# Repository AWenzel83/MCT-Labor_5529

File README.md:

# MCT-Labor_5529
Laboraufbau mit MSP-EXP430f5529-LP

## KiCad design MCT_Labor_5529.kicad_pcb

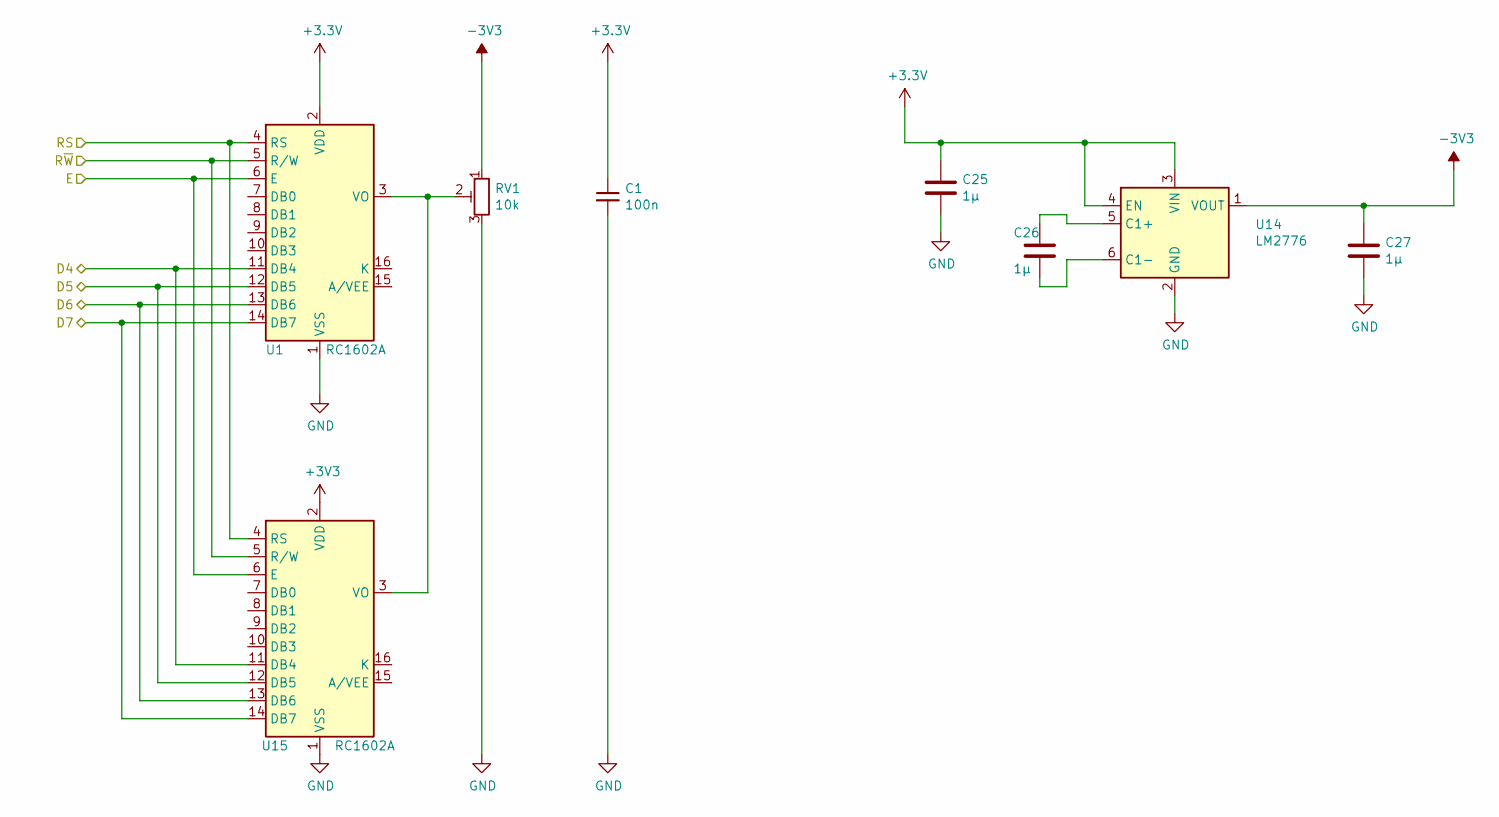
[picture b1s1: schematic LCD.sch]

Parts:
C1: 100n; C_0603_1608Metric_Pad1.05x0.95mm_HandSolder
C25, C26, C27: 1µ; C_0603_1608Metric_Pad1.05x0.95mm_HandSolder
RV1: 10k; Potentiometer_Bourns_3296P_Horizontal
U1: RC1602A; WC1602A
U14: LM2776; SOT-23-6
U15: RC1602A

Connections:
-3V3: C27.1, RV1.1, U14.1 (VOUT)
/LCD/D4: U1.11 (DB4), U15.11 (DB4); also elsewhere on the board
/LCD/D5: U1.12 (DB5), U15.12 (DB5); also elsewhere on the board
/LCD/D6: U1.13 (DB6), U15.13 (DB6); also elsewhere on the board
/LCD/D7: U1.14 (DB7), U15.14 (DB7); also elsewhere on the board
/LCD/E: U1.6 (E), U15.6 (E); also elsewhere on the board
/Launchpad/P6.4: U1.5 (R/W), U15.5 (R/W); also elsewhere on the board
/Launchpad/P6.5: U1.4 (RS), U15.4 (RS); also elsewhere on the board
unnamed: C26.1, U14.5 (C1+)
unnamed: C26.2, U14.6 (C1-)
unnamed: RV1.2, U1.3 (VO), U15.3 (VO)

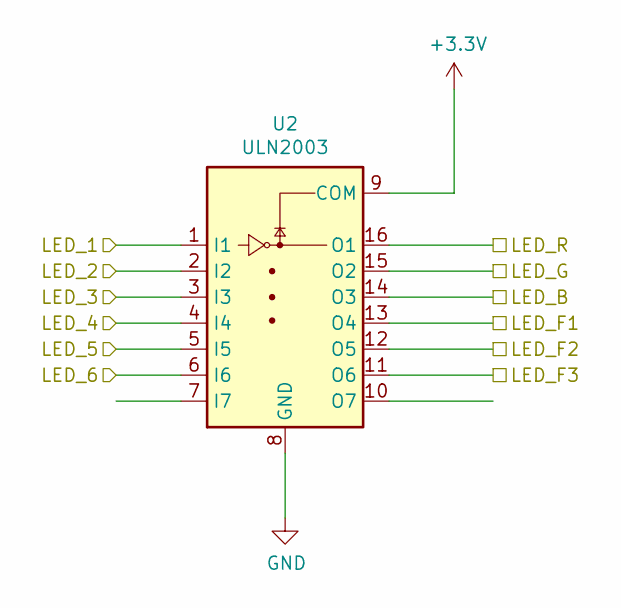
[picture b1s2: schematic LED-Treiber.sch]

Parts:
U2: ULN2003; SOIC-16_3.9x9.9mm_P1.27mm

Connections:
/Button_decoder/LED_F1: U2.13 (O4); also elsewhere on the board
/Button_decoder/LED_F2: U2.12 (O5); also elsewhere on the board
/Button_decoder/LED_F3: U2.11 (O6); also elsewhere on the board
/LED-Treiber/LED_1: U2.1 (I1); also elsewhere on the board
/LED-Treiber/LED_2: U2.2 (I2); also elsewhere on the board
/LED-Treiber/LED_3: U2.3 (I3); also elsewhere on the board
/LED-Treiber/LED_4: U2.4 (I4); also elsewhere on the board
/LED-Treiber/LED_5: U2.5 (I5); also elsewhere on the board
/LED-Treiber/LED_6: U2.6 (I6); also elsewhere on the board
/LED-Treiber/LED_B: U2.14 (O3); also elsewhere on the board
/LED-Treiber/LED_G: U2.15 (O2); also elsewhere on the board
/LED-Treiber/LED_R: U2.16 (O1); also elsewhere on the board

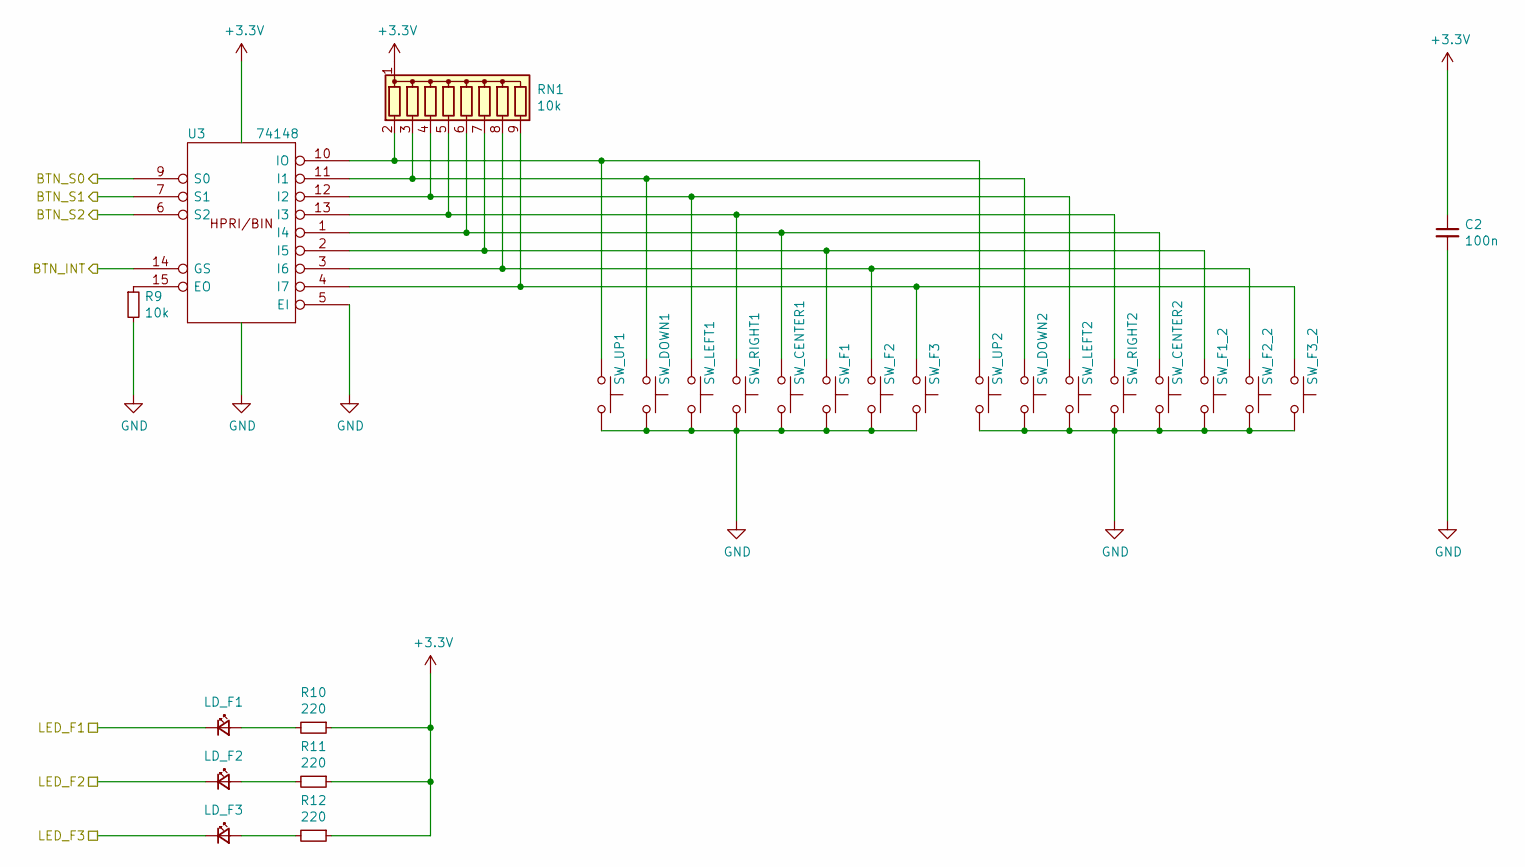
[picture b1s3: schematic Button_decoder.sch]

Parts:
C2: 100n; C_0603_1608Metric_Pad1.05x0.95mm_HandSolder
LD_F1, LD_F2, LD_F3: LED_Small; LED_D3.0mm
R9: 10k; R_0603_1608Metric_Pad1.05x0.95mm_HandSolder
R10, R11, R12: 220; R_0603_1608Metric_Pad1.05x0.95mm_HandSolder
RN1: 10k; R_Array_SIP9
SW_CENTER1: SW_MEC_5G; SW_MEC_5GSH9
SW_CENTER2: SW_MEC_5G; SW_SPST_Omron_B3FS-100xP
SW_DOWN1: SW_MEC_5G; SW_MEC_5GSH9
SW_DOWN2: SW_MEC_5G; SW_SPST_Omron_B3FS-100xP
SW_F1, SW_F2, SW_F3: SW_MEC_5G; SW_MEC_5GSH9
SW_F1_2: SW_MEC_5; SW_SPST_Omron_B3FS-100xP
SW_F2_2, SW_F3_2: SW_MEC_5G; SW_SPST_Omron_B3FS-100xP
SW_LEFT1: SW_MEC_5G; SW_MEC_5GSH9
SW_LEFT2: SW_MEC_5G; SW_SPST_Omron_B3FS-100xP
SW_RIGHT1: SW_MEC_5G; SW_MEC_5GSH9
SW_RIGHT2: SW_MEC_5G; SW_SPST_Omron_B3FS-100xP
SW_UP1: SW_MEC_5G; SW_MEC_5GSH9
SW_UP2: SW_MEC_5G; SW_SPST_Omron_B3FS-100xP
U3: 74148; SOIC-16_3.9x9.9mm_P1.27mm

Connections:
/Button_decoder/BTN_INT: U3.14 (GS); also elsewhere on the board
/Button_decoder/BTN_S0: U3.9 (S0); also elsewhere on the board
/Button_decoder/BTN_S1: U3.7 (S1); also elsewhere on the board
/Button_decoder/BTN_S2: U3.6 (S2); also elsewhere on the board
/Button_decoder/LED_F1: LD_F1.1 (K); also elsewhere on the board
/Button_decoder/LED_F2: LD_F2.1 (K); also elsewhere on the board
/Button_decoder/LED_F3: LD_F3.1 (K); also elsewhere on the board
unnamed: LD_F1.2 (A), R10.2
unnamed: LD_F2.2 (A), R11.2
unnamed: LD_F3.2 (A), R12.2
unnamed: R9.1, U3.15 (EO)
unnamed: RN1.2 (R1), SW_UP1.1 (A), SW_UP1.2 (A), SW_UP2.1 (A), SW_UP2.2 (A), U3.10 (IO)
unnamed: RN1.3 (R2), SW_DOWN1.1 (A), SW_DOWN1.2 (A), SW_DOWN2.1 (A), SW_DOWN2.2 (A), U3.11 (I1)
unnamed: RN1.4 (R3), SW_LEFT1.1 (A), SW_LEFT1.2 (A), SW_LEFT2.1 (A), SW_LEFT2.2 (A), U3.12 (I2)
unnamed: RN1.5 (R4), SW_RIGHT1.1 (A), SW_RIGHT1.2 (A), SW_RIGHT2.1 (A), SW_RIGHT2.2 (A), U3.13 (I3)
unnamed: RN1.6 (R5), SW_CENTER1.1 (A), SW_CENTER1.2 (A), SW_CENTER2.1 (A), SW_CENTER2.2 (A), U3.1 (I4)
unnamed: RN1.7 (R6), SW_F1.1 (A), SW_F1.2 (A), SW_F1_2.1 (A), SW_F1_2.2 (A), U3.2 (I5)
unnamed: RN1.8 (R7), SW_F2.1 (A), SW_F2.2 (A), SW_F2_2.1 (A), SW_F2_2.2 (A), U3.3 (I6)
unnamed: RN1.9 (R8), SW_F3.1 (A), SW_F3.2 (A), SW_F3_2.1 (A), SW_F3_2.2 (A), U3.4 (I7)

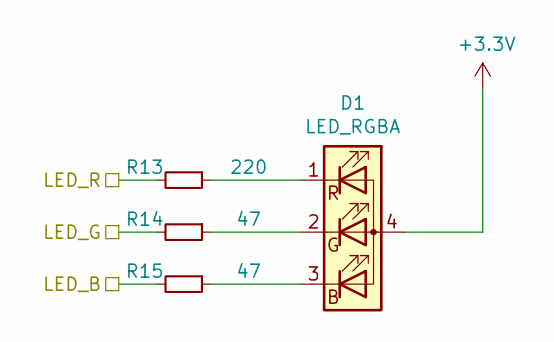
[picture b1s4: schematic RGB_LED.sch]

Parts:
D1: LED_RGBA; LED_Cree-PLCC4_3.2x2.8mm_CCW
R13: 220; R_0603_1608Metric_Pad1.05x0.95mm_HandSolder
R14, R15: 47; R_0603_1608Metric_Pad1.05x0.95mm_HandSolder

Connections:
/LED-Treiber/LED_B: R15.2; also elsewhere on the board
/LED-Treiber/LED_G: R14.2; also elsewhere on the board
/LED-Treiber/LED_R: R13.2; also elsewhere on the board
unnamed: D1.1 (RK), R13.1
unnamed: D1.2 (GK), R14.1
unnamed: D1.3 (BK), R15.1

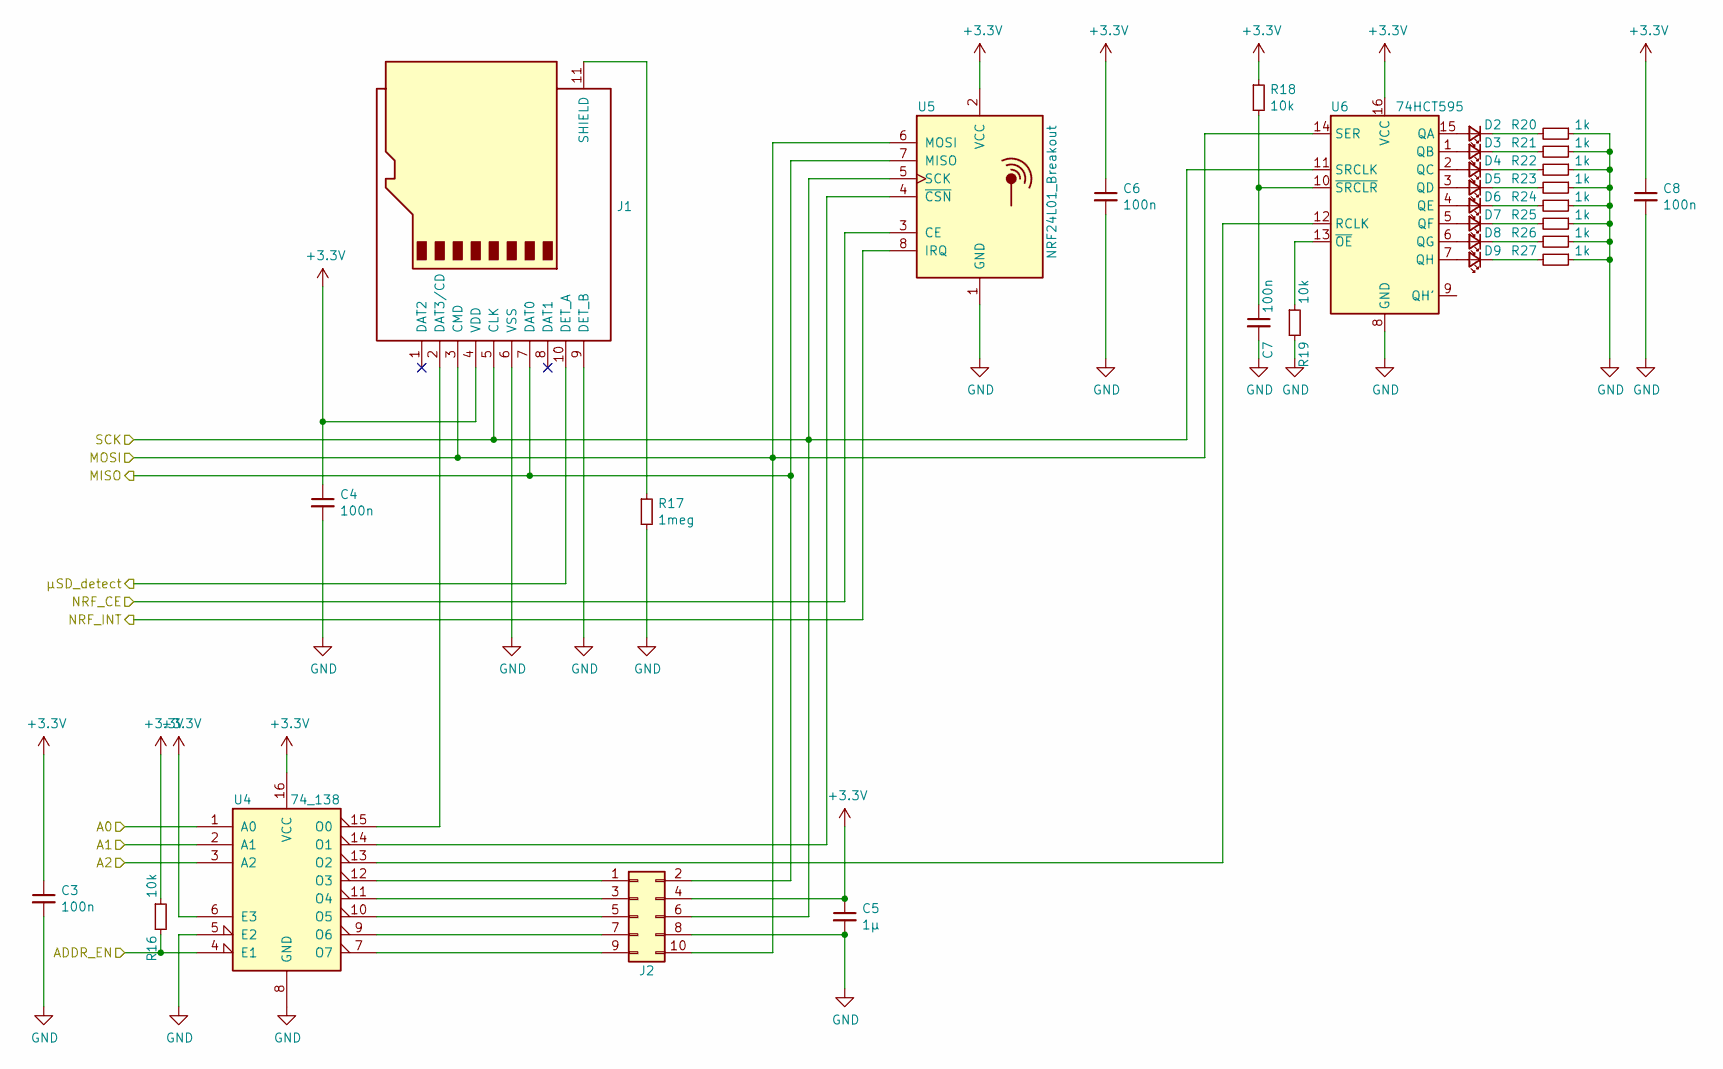
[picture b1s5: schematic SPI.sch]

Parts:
C3, C4, C6, C7, C8: 100n; C_0603_1608Metric_Pad1.05x0.95mm_HandSolder
C5: 1µ; C_0603_1608Metric_Pad1.05x0.95mm_HandSolder
D2, D3, D4, D5, D6, D7, D8, D9: LED_Small; LED_0603_1608Metric_Pad1.05x0.95mm_HandSolder
J1: Micro_SD_Card_Det; microSD_HC_Hirose_DM3D-SF
J2: Conn_02x05_Odd_Even; PinHeader_2x05_P2.54mm_Vertical
R16, R18, R19: 10k; R_0603_1608Metric_Pad1.05x0.95mm_HandSolder
R17: 1meg; R_0603_1608Metric_Pad1.05x0.95mm_HandSolder
R20, R21, R22, R23, R24, R25, R26, R27: 1k; R_0603_1608Metric_Pad1.05x0.95mm_HandSolder
U4: 74_138; SOIC-16_3.9x9.9mm_P1.27mm
U5: NRF24L01_Breakout; nRF24L01_Breakout
U6: 74HCT595; SOIC-16_3.9x9.9mm_P1.27mm

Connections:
/Launchpad/P3.2: J1.5 (CLK), J2.6, U5.5 (SCK), U6.11 (SRCLK); also elsewhere on the board
/Launchpad/P7.4: J1.10 (DET_A); also elsewhere on the board
/SPI/A0: U4.1 (A0); also elsewhere on the board
/SPI/A1: U4.2 (A1); also elsewhere on the board
/SPI/A2: U4.3 (A2); also elsewhere on the board
/SPI/ADDR_EN: R16.2, U4.4 (E1); also elsewhere on the board
/SPI/MISO: J1.7 (DAT0), J2.2, U5.7 (MISO); also elsewhere on the board
/SPI/MOSI: J1.3 (CMD), J2.10, U5.6 (MOSI), U6.14 (SER); also elsewhere on the board
/SPI/NRF_CE: U5.3 (CE); also elsewhere on the board
/SPI/NRF_INT: U5.8 (IRQ); also elsewhere on the board
unnamed: C7.1, R18.2, U6.10 (~SRCLR)
unnamed: D2.1 (K), R20.2
unnamed: D2.2 (A), U6.15 (QA)
unnamed: D3.1 (K), R21.2
unnamed: D3.2 (A), U6.1 (QB)
unnamed: D4.1 (K), R22.2
unnamed: D4.2 (A), U6.2 (QC)
unnamed: D5.1 (K), R23.2
unnamed: D5.2 (A), U6.3 (QD)
unnamed: D6.1 (K), R24.2
unnamed: D6.2 (A), U6.4 (QE)
unnamed: D7.1 (K), R25.2
unnamed: D7.2 (A), U6.5 (QF)
unnamed: D8.1 (K), R26.2
unnamed: D8.2 (A), U6.6 (QG)
unnamed: D9.1 (K), R27.2
unnamed: D9.2 (A), U6.7 (QH)
unnamed: J1.2 (DAT3/CD), U4.15 (O0)
unnamed: J1.11 (SHIELD), R17.1
unnamed: J2.1, U4.12 (O3)
unnamed: J2.3, U4.11 (O4)
unnamed: J2.5, U4.10 (O5)
unnamed: J2.7, U4.9 (O6)
unnamed: J2.9, U4.7 (O7)
unnamed: R19.1, U6.13 (~OE)
unnamed: U4.13 (O2), U6.12 (RCLK)
unnamed: U4.14 (O1), U5.4 (~CSN)

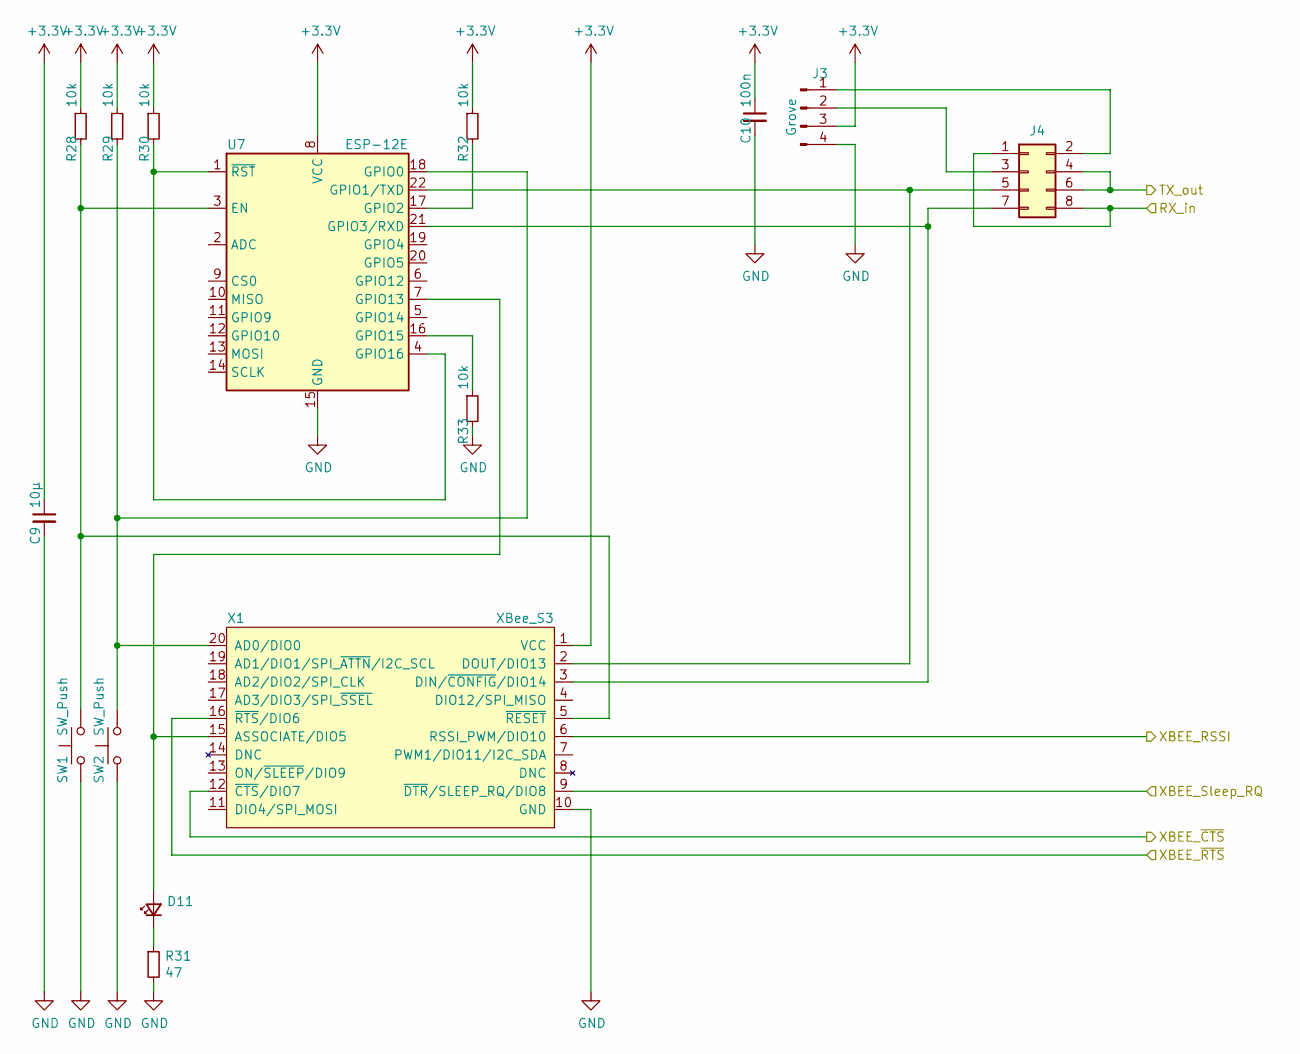
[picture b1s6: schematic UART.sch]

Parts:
C9: 10µ; C_1206_3216Metric_Pad1.42x1.75mm_HandSolder
C10: 100n; C_0603_1608Metric_Pad1.05x0.95mm_HandSolder
D11: LED_Small; LED_0603_1608Metric_Pad1.05x0.95mm_HandSolder
J3: Grove; NS-Tech_Grove_1x04_P2mm_Vertical
J4: Conn_02x04_Odd_Even; PinHeader_2x04_P2.54mm_Vertical
R28, R29, R30, R32, R33: 10k; R_0603_1608Metric_Pad1.05x0.95mm_HandSolder
R31: 47; R_0603_1608Metric_Pad1.05x0.95mm_HandSolder
SW1, SW2: SW_Push; SW_Tactile_SPST_Angled_PTS645Vx39-2LFS
U7: ESP-12E
X1: XBee_S3; XBEE_THT

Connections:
/Launchpad/P1.2_XBEE: X1.9 (~DTR~/SLEEP_RQ/DIO8); also elsewhere on the board
/Launchpad/P1.3_XBEE: X1.12 (~CTS~/DIO7); also elsewhere on the board
/Launchpad/P1.4_XBEE: X1.16 (~RTS~/DIO6); also elsewhere on the board
/Launchpad/P1.5_XBEE: X1.6 (RSSI_PWM/DIO10); also elsewhere on the board
/Launchpad/P3.3: J4.1, J4.8; also elsewhere on the board
/Launchpad/P3.4: J4.4, J4.6; also elsewhere on the board
unnamed: D11.1 (K), R31.1
unnamed: J3.1, J4.2
unnamed: J3.2, J4.3
unnamed: R28.2, SW1.2, U7.3 (EN), X1.5 (~RESET)

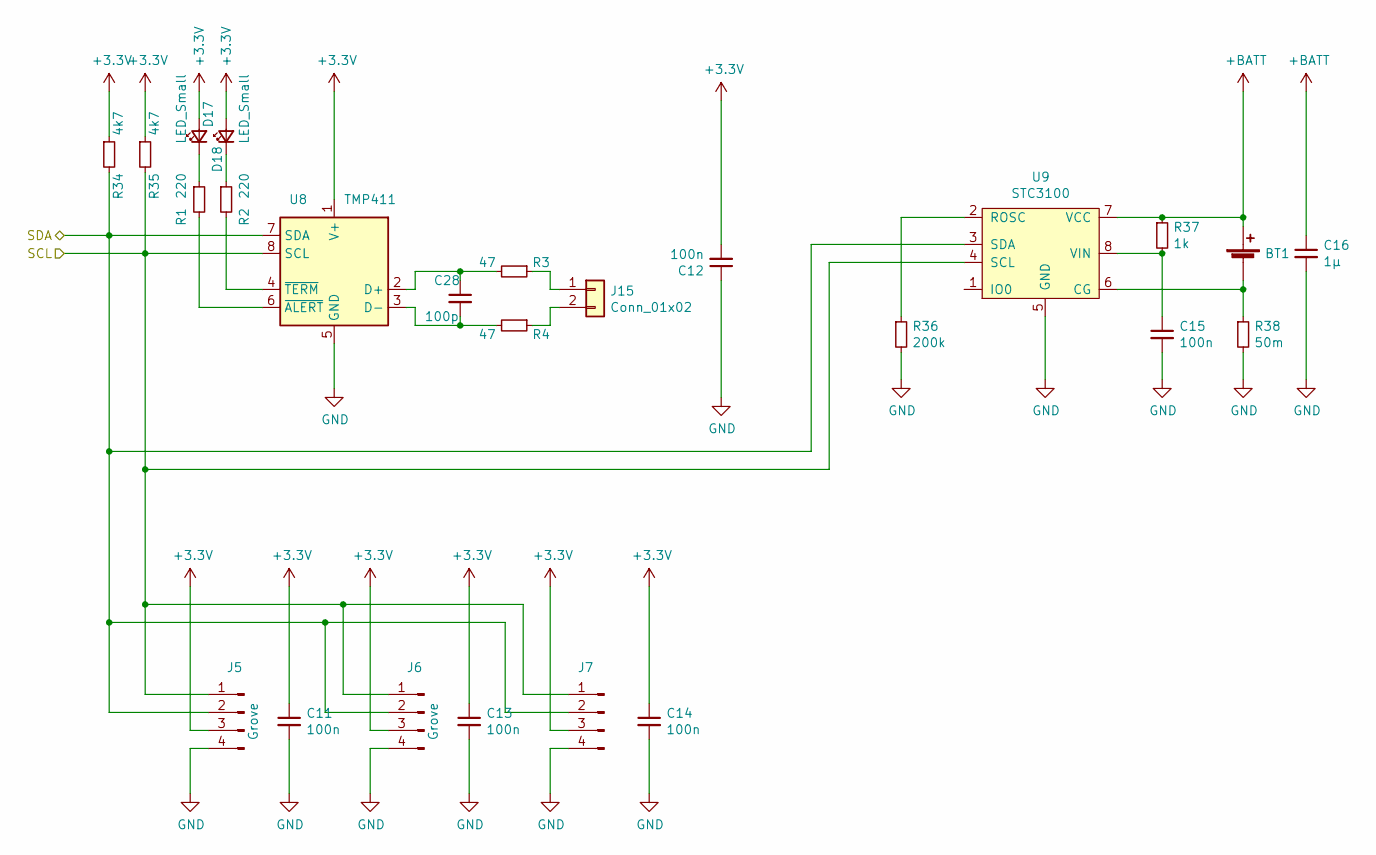
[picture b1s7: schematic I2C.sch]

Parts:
BT1: 18650_Cell; BatteryHolder_Keystone_1042_1x18650
C11, C12, C13, C14, C15: 100n; C_0603_1608Metric_Pad1.05x0.95mm_HandSolder
C16: 1µ; C_0603_1608Metric_Pad1.05x0.95mm_HandSolder
C28: 100p; C_0603_1608Metric_Pad1.05x0.95mm_HandSolder
D17, D18: LED_Small; LED_0603_1608Metric_Pad1.05x0.95mm_HandSolder
J5, J6: Grove; NS-Tech_Grove_1x04_P2mm_Vertical
J7: Conn_01x04_Male; PinHeader_1x04_P2.54mm_Vertical
J15: Conn_01x02; PinHeader_1x02_P2.54mm_Vertical
R1, R2: 220; R_0603_1608Metric_Pad1.05x0.95mm_HandSolder
R3, R4: 47; R_0603_1608Metric_Pad1.05x0.95mm_HandSolder
R34, R35: 4k7; R_0603_1608Metric_Pad1.05x0.95mm_HandSolder
R36: 200k; R_0603_1608Metric_Pad1.05x0.95mm_HandSolder
R37: 1k; R_0603_1608Metric_Pad1.05x0.95mm_HandSolder
R38: 50m; R_1206_3216Metric_Pad1.42x1.75mm_HandSolder
U8: TMP411; SO-8_3.9x4.9mm_P1.27mm
U9: STC3100; MSOP-8_3x3mm_P0.65mm

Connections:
+BATT: BT1.1 (+), C16.1, R37.1, U9.7 (VCC); also elsewhere on the board
/Launchpad/P4.1: J5.2, J6.2, J7.2, R34.2, U8.7 (SDA), U9.3 (SDA); also elsewhere on the board
/Launchpad/P4.2: J5.1, J6.1, J7.1, R35.2, U8.8 (SCL), U9.4 (SCL); also elsewhere on the board
unnamed: BT1.2 (-), R38.1, U9.6 (CG)
unnamed: C15.1, R37.2, U9.8 (VIN)
unnamed: C28.1, R3.2, U8.2 (D+)
unnamed: C28.2, R4.2, U8.3 (D-)
unnamed: D17.1 (K), R1.1
unnamed: D18.1 (K), R2.1
unnamed: J15.1, R3.1
unnamed: J15.2, R4.1
unnamed: R1.2, U8.6 (~ALERT)
unnamed: R2.2, U8.4 (~TERM)
unnamed: R36.1, U9.2 (ROSC)

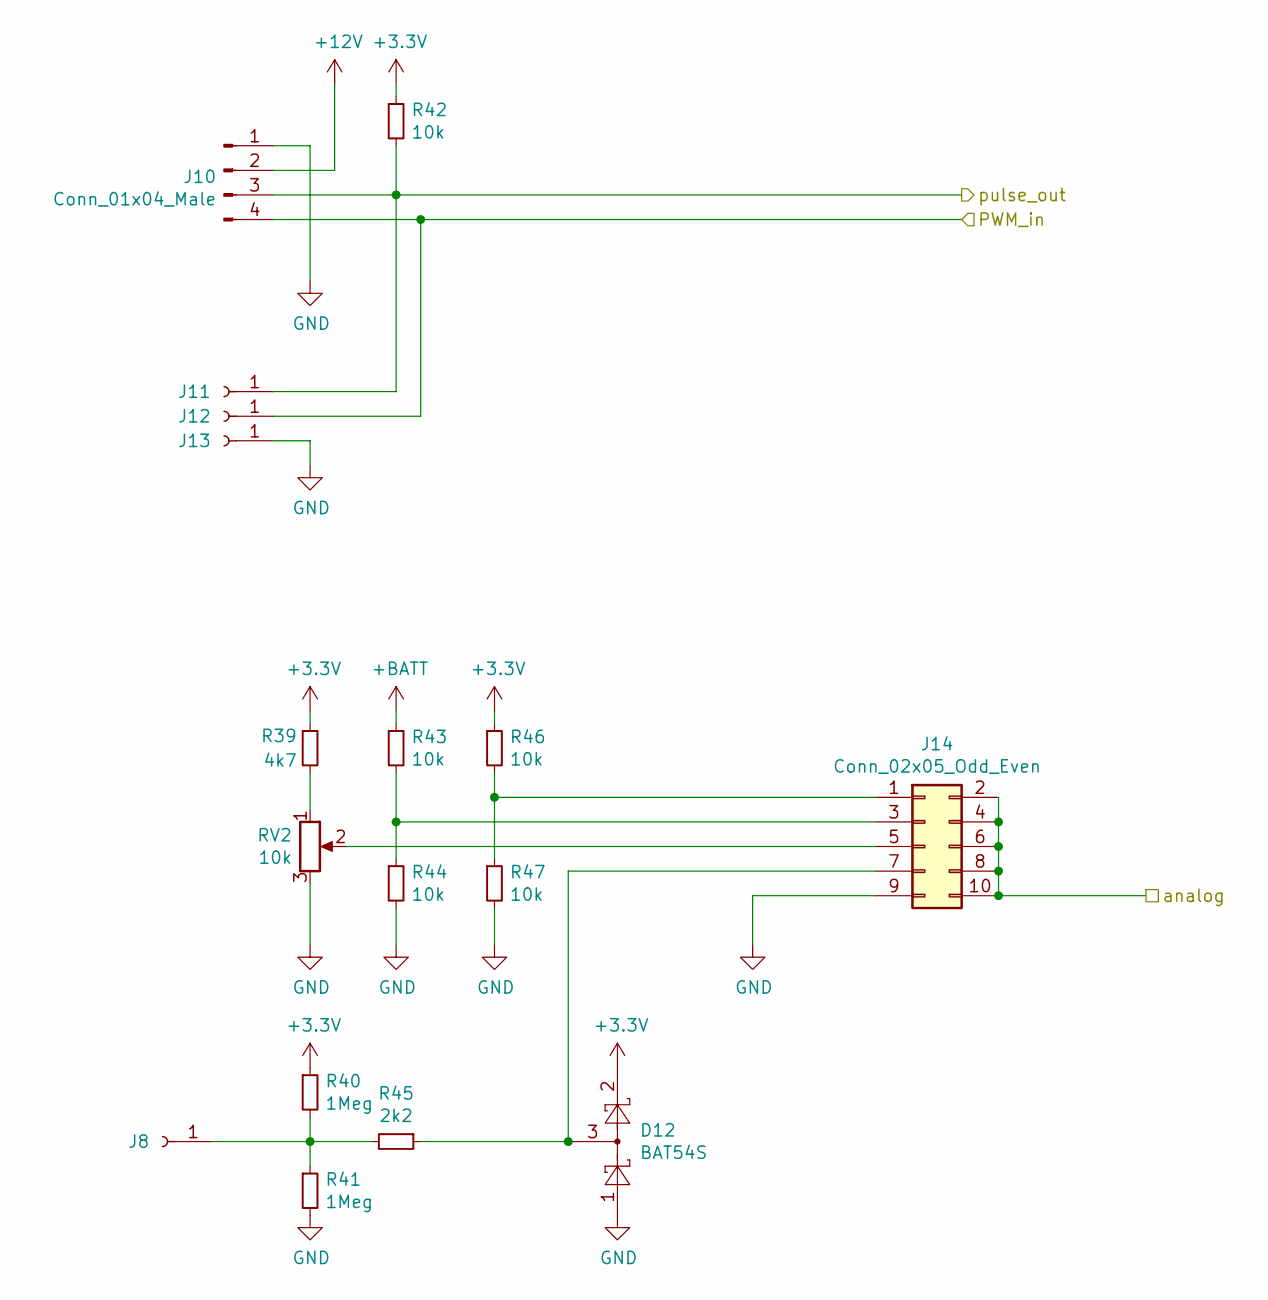
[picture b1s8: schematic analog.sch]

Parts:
D12: BAT54S; SOT-23
J8, J11, J12, J13: Conn_01x01_Female; 2mm_Socket
J10: Conn_01x04_Male; Molex_KK-254_AE-6410-04A_1x04_P2.54mm_Vertical
J14: Conn_02x05_Odd_Even; PinHeader_2x05_P2.54mm_Vertical
R39: 4k7; R_0603_1608Metric_Pad1.05x0.95mm_HandSolder
R40, R41: 1Meg; R_0603_1608Metric_Pad1.05x0.95mm_HandSolder
R42, R43, R44, R46, R47: 10k; R_0603_1608Metric_Pad1.05x0.95mm_HandSolder
R45: 2k2; R_0603_1608Metric_Pad1.05x0.95mm_HandSolder
RV2: 10k; Potentiometer_Alps_RK09K_Single_Vertical

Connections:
+12V: J10.2; also elsewhere on the board
+BATT: R43.1; also elsewhere on the board
/Launchpad/P1.5_FAN: J10.4, J12.1; also elsewhere on the board
/Launchpad/P1.6: J10.3, J11.1, R42.2; also elsewhere on the board
/Launchpad/P7.0: J14.2, J14.4, J14.6, J14.8, J14.10; also elsewhere on the board
unnamed: D12.3, J14.7, R45.1
unnamed: J8.1, R40.2, R41.1, R45.2
unnamed: J14.1, R46.2, R47.1
unnamed: J14.3, R43.2, R44.1
unnamed: J14.5, RV2.2
unnamed: R39.2, RV2.1

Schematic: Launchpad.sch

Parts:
C17: 1u; C_0603_1608Metric_Pad1.05x0.95mm_HandSolder
C18, C21: 10µ; C_1206_3216Metric_Pad1.42x1.75mm_HandSolder
C19, C20: 4µ7; C_1206_3216Metric_Pad1.42x1.75mm_HandSolder
C22, C23: 100n; C_0603_1608Metric_Pad1.05x0.95mm_HandSolder
C24: 10u; C_1206_3216Metric_Pad1.42x1.75mm_HandSolder
D13: MBRS120; D_SMB_Handsoldering
D14, D16: BAT54C; SOT-23
D15: LED_Small; LED_0603_1608Metric
J18: Screw_Terminal_01x02; TerminalBlock_Phoenix_MKDS-3-2-5.08_1x02_P5.08mm_Horizontal
JP1, JP3, JP4, JP5: JP_3; PinHeader_1x03_P2.54mm_Vertical
L1: 3.3u; L_Coilcraft_XxL4040_handsolder
Q1: BSS138; SOT-23
R48: 1.5M; R_0603_1608Metric_Pad1.05x0.95mm_HandSolder
R49, R51, R53: 10k; R_0603_1608Metric_Pad1.05x0.95mm_HandSolder
R50: 2k2; R_0603_1608Metric_Pad1.05x0.95mm_HandSolder
R52: 220; R_0603_1608Metric_Pad1.05x0.95mm_HandSolder
R54: 100k; R_0603_1608Metric_Pad1.05x0.95mm_HandSolder
SW3: SW_SPDT; SS_13PLP
U10: msp-exp430f5529-LP; TI_Launchpad
U11: MCP73831; SOT-23-5
U12: TPS73733; SOT-223-6
U13: TLV61048; SOT-23-6

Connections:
12V_Enable: U10.31 (P8.2), U13.4 (EN)
+12V: C24.1, D13.1 (K), R48.1; also elsewhere on the board
+BATT: C20.1, D16.1, U11.3 (VBAT); also elsewhere on the board
/Button_decoder/BTN_INT: U10.19 (P2.0); also elsewhere on the board
/Button_decoder/BTN_S0: U10.18 (P2.2); also elsewhere on the board
/Button_decoder/BTN_S1: U10.12 (P2.3); also elsewhere on the board
/Button_decoder/BTN_S2: U10.39 (P2.4); also elsewhere on the board
/LCD/D4: U10.23 (P6.0); also elsewhere on the board
/LCD/D5: U10.24 (P6.1); also elsewhere on the board
/LCD/D6: U10.25 (P6.2); also elsewhere on the board
/LCD/D7: U10.26 (P6.3); also elsewhere on the board
/LCD/E: U10.6 (P6.6); also elsewhere on the board
/LED-Treiber/LED_1: JP1.1 (A); also elsewhere on the board
/LED-Treiber/LED_2: JP3.1 (A); also elsewhere on the board
/LED-Treiber/LED_3: JP4.1 (A); also elsewhere on the board
/LED-Treiber/LED_4: U10.30 (P3.5); also elsewhere on the board
/LED-Treiber/LED_5: U10.29 (P3.6); also elsewhere on the board
/LED-Treiber/LED_6: U10.32 (P3.7); also elsewhere on the board
/Launchpad/P1.2_XBEE: JP1.3 (B); also elsewhere on the board
/Launchpad/P1.3_XBEE: JP3.3 (B); also elsewhere on the board
/Launchpad/P1.4_XBEE: JP4.3 (B); also elsewhere on the board
/Launchpad/P1.5_FAN: JP5.1 (A); also elsewhere on the board
/Launchpad/P1.5_XBEE: JP5.3 (B); also elsewhere on the board
/Launchpad/P1.6: U10.5 (P1.6); also elsewhere on the board
/Launchpad/P3.2: U10.7 (P3.2); also elsewhere on the board
/Launchpad/P3.3: U10.4 (P3.3); also elsewhere on the board
/Launchpad/P3.4: U10.3 (P3.4); also elsewhere on the board
/Launchpad/P4.1: U10.10 (P4.1); also elsewhere on the board
/Launchpad/P4.2: U10.9 (P4.2); also elsewhere on the board
/Launchpad/P6.4: U10.27 (P6.4); also elsewhere on the board
/Launchpad/P6.5: U10.2 (P6.5); also elsewhere on the board
/Launchpad/P7.0: U10.28 (P7.0); also elsewhere on the board
/Launchpad/P7.4: U10.17 (P7.4); also elsewhere on the board
/SPI/A0: U10.40 (P2.5); also elsewhere on the board
/SPI/A1: U10.13 (P2.6); also elsewhere on the board
/SPI/A2: U10.8 (P2.7); also elsewhere on the board
/SPI/ADDR_EN: U10.11 (P8.1); also elsewhere on the board
/SPI/MISO: U10.14 (P3.1); also elsewhere on the board
/SPI/MOSI: U10.15 (P3.0); also elsewhere on the board
/SPI/NRF_CE: U10.33 (P4.0); also elsewhere on the board
/SPI/NRF_INT: U10.34 (P4.3); also elsewhere on the board
unnamed: C17.1, C21.1, D16.3, L1.1, SW3.2 (B), U12.1 (IN), U13.5 (VIN)
unnamed: C22.1, U12.4 (FB)
unnamed: D13.2 (A), L1.2, U13.1 (SW)
unnamed: D15.1 (K), R52.1
unnamed: JP1.2 (C), U10.35 (P1.2)
unnamed: JP3.2 (C), U10.36 (P1.3)
unnamed: JP4.2 (C), U10.37 (P1.4)
unnamed: JP5.2 (C), U10.38 (P1.5)
unnamed: Q1.3 (D), R50.2
unnamed: R48.2, R54.1, U13.3 (FB)
unnamed: R50.1, R51.1, U11.5 (PROG)
unnamed: R52.2, U11.1 (STAT)
VBUS: D14.2, U10.21 (+5V)
VDC: C18.1, D14.1, J18.1, Q1.1 (G), R49.1
VDD: C19.1, D14.3, D15.2 (A), D16.2, R53.1, SW3.1 (A), U11.4 (VDD), U12.5 (EN)

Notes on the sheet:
Der 3V3 Jumper auf dem Launchpad muss gezogen sein

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
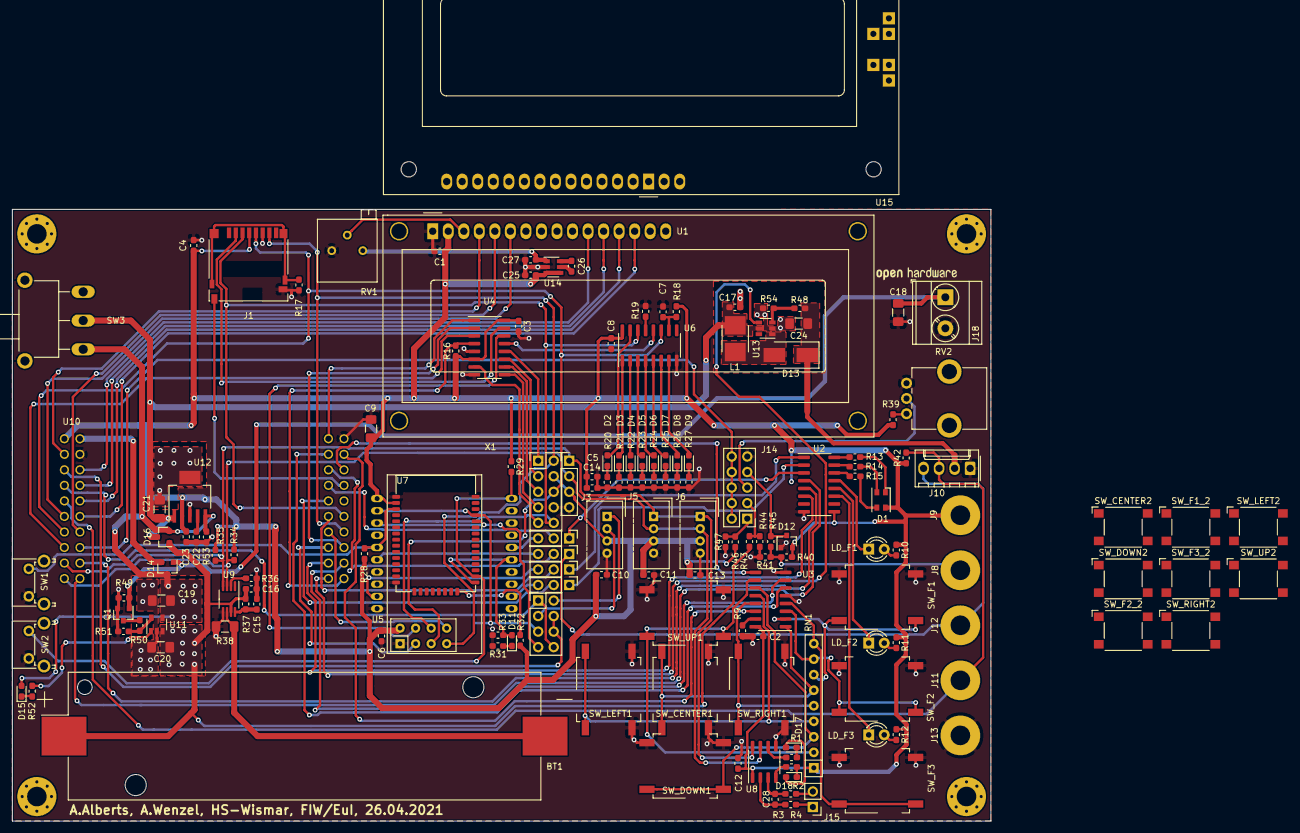
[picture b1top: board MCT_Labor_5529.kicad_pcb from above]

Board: 2 copper layers, 160.0 x 100.0 mm, 159 parts (0 on the bottom side), 136 nets.

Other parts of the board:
J9: Conn_01x01_Female; 2mm_Socket
e: MountingHole_3.2mm_M3_Pad_Via

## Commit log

2020-06-16 Projekt angelegt
    Projekt angelegt
2020-06-16 Bibliothek hinzugefügt
2020-06-16 LCD-File hinzugefügt
2020-06-19 Erster Entwurf fürs Pinout
2020-06-19 Footprintbibliothek eingefügt
2020-06-19 Schaltplan angefangen
2020-06-25 Blockschaltbild komplett v1
2020-07-01 Erste fertige Version
2020-07-03 Externe Spannungsversorgung
2020-07-03 da war noch nicht alles gespeichert
2020-07-07 Bauteile grob platziert
2020-07-13 Alle Bauteile platziert
    Alle Bauteile sind grob plaziert.
    Einige Bauteile sollten noch umplaziert werden (u. a. die Jumper links neben Groov-Con, RGB-LED,).
2020-07-14 Routing der rechten Platinenhälfte
2020-07-16 Routing komplett
2020-07-17 Kleine Änderungen
2020-07-27 Release V1.0
    Kleinigkeiten verändert
    Bestückungsdruck angepasst
2020-07-28 Anpassungen am Lüfteranschluss und den LEDs
    -Lüfteranschluss verändert
    -> 12V-Versorgung eingefügt
    -LED & LCD auf 3,3V umgestellt
    -> Ladungspunpe für neg. Kontrastspannung
    -keine 5V Versorgung mehr
2020-07-28 Kleine Änderungen
    Fehler in Kupferflächen und Bestückungsdruck angepasst.
2020-07-29 Kleine Anpassungen
2020-08-04 LM75 durch TMP411 ersetzt
    -Temperatursensor getauscht
    -3,3V 2mm Buchse hinzugeügt
    -Bohrlöcher wieder eingefügt
2020-08-04 LEDs beim TMP411 hinzugegfügt
2020-08-05 Erster vorab Release - Fertigungsdaten erstellt
2020-08-05 TODO-Liste hinzugefügt
2021-01-14 minor glitches
2021-01-14 Kupferfläche auf Top -> GND, 3,3V neu gerouted
2021-01-21 Aktuell gefertigte Variante
2021-01-21 Fertigungsdaten v1.0
2021-04-22 Open Hardware Logo eingefügt
2021-04-22 Vorbereitet für Release für Group-Buy
2021-04-26 Switched ESP8266F to MICRO32
2021-04-28 Alternative Footprints für Taster und LCD eingefügt
